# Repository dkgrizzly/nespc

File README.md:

# NES as an 8-Bit PC

This is very much a work in progress, and should be treated as such.

Based on the work done by [Joseph Marlin](https://github.com/jmarlin/) on his YouTube channel [TrackZero](https://www.youtube.com/c/TrackZeroFutzin).
Attaching a standard floppy disk controller (FDC) to a NES-001 game console with BASIC and Monitor in ROM.

I've separated the FDC to a mezzanine card which can be extended outside the case on a 40-pin IDC cable.
Partly due to the relative scarcity of the chips, and partly due to the complexity of the signal routing involved.
The FDC and additonal expansion cards share an 8-bit data and 8-bit address bus. The bus has eight select lines in addition to the FDC selects.

Expansion cards should be connected with 40-pin IDC edge connectors. The expansion bus cable should have three twists as show in expansion.txt.

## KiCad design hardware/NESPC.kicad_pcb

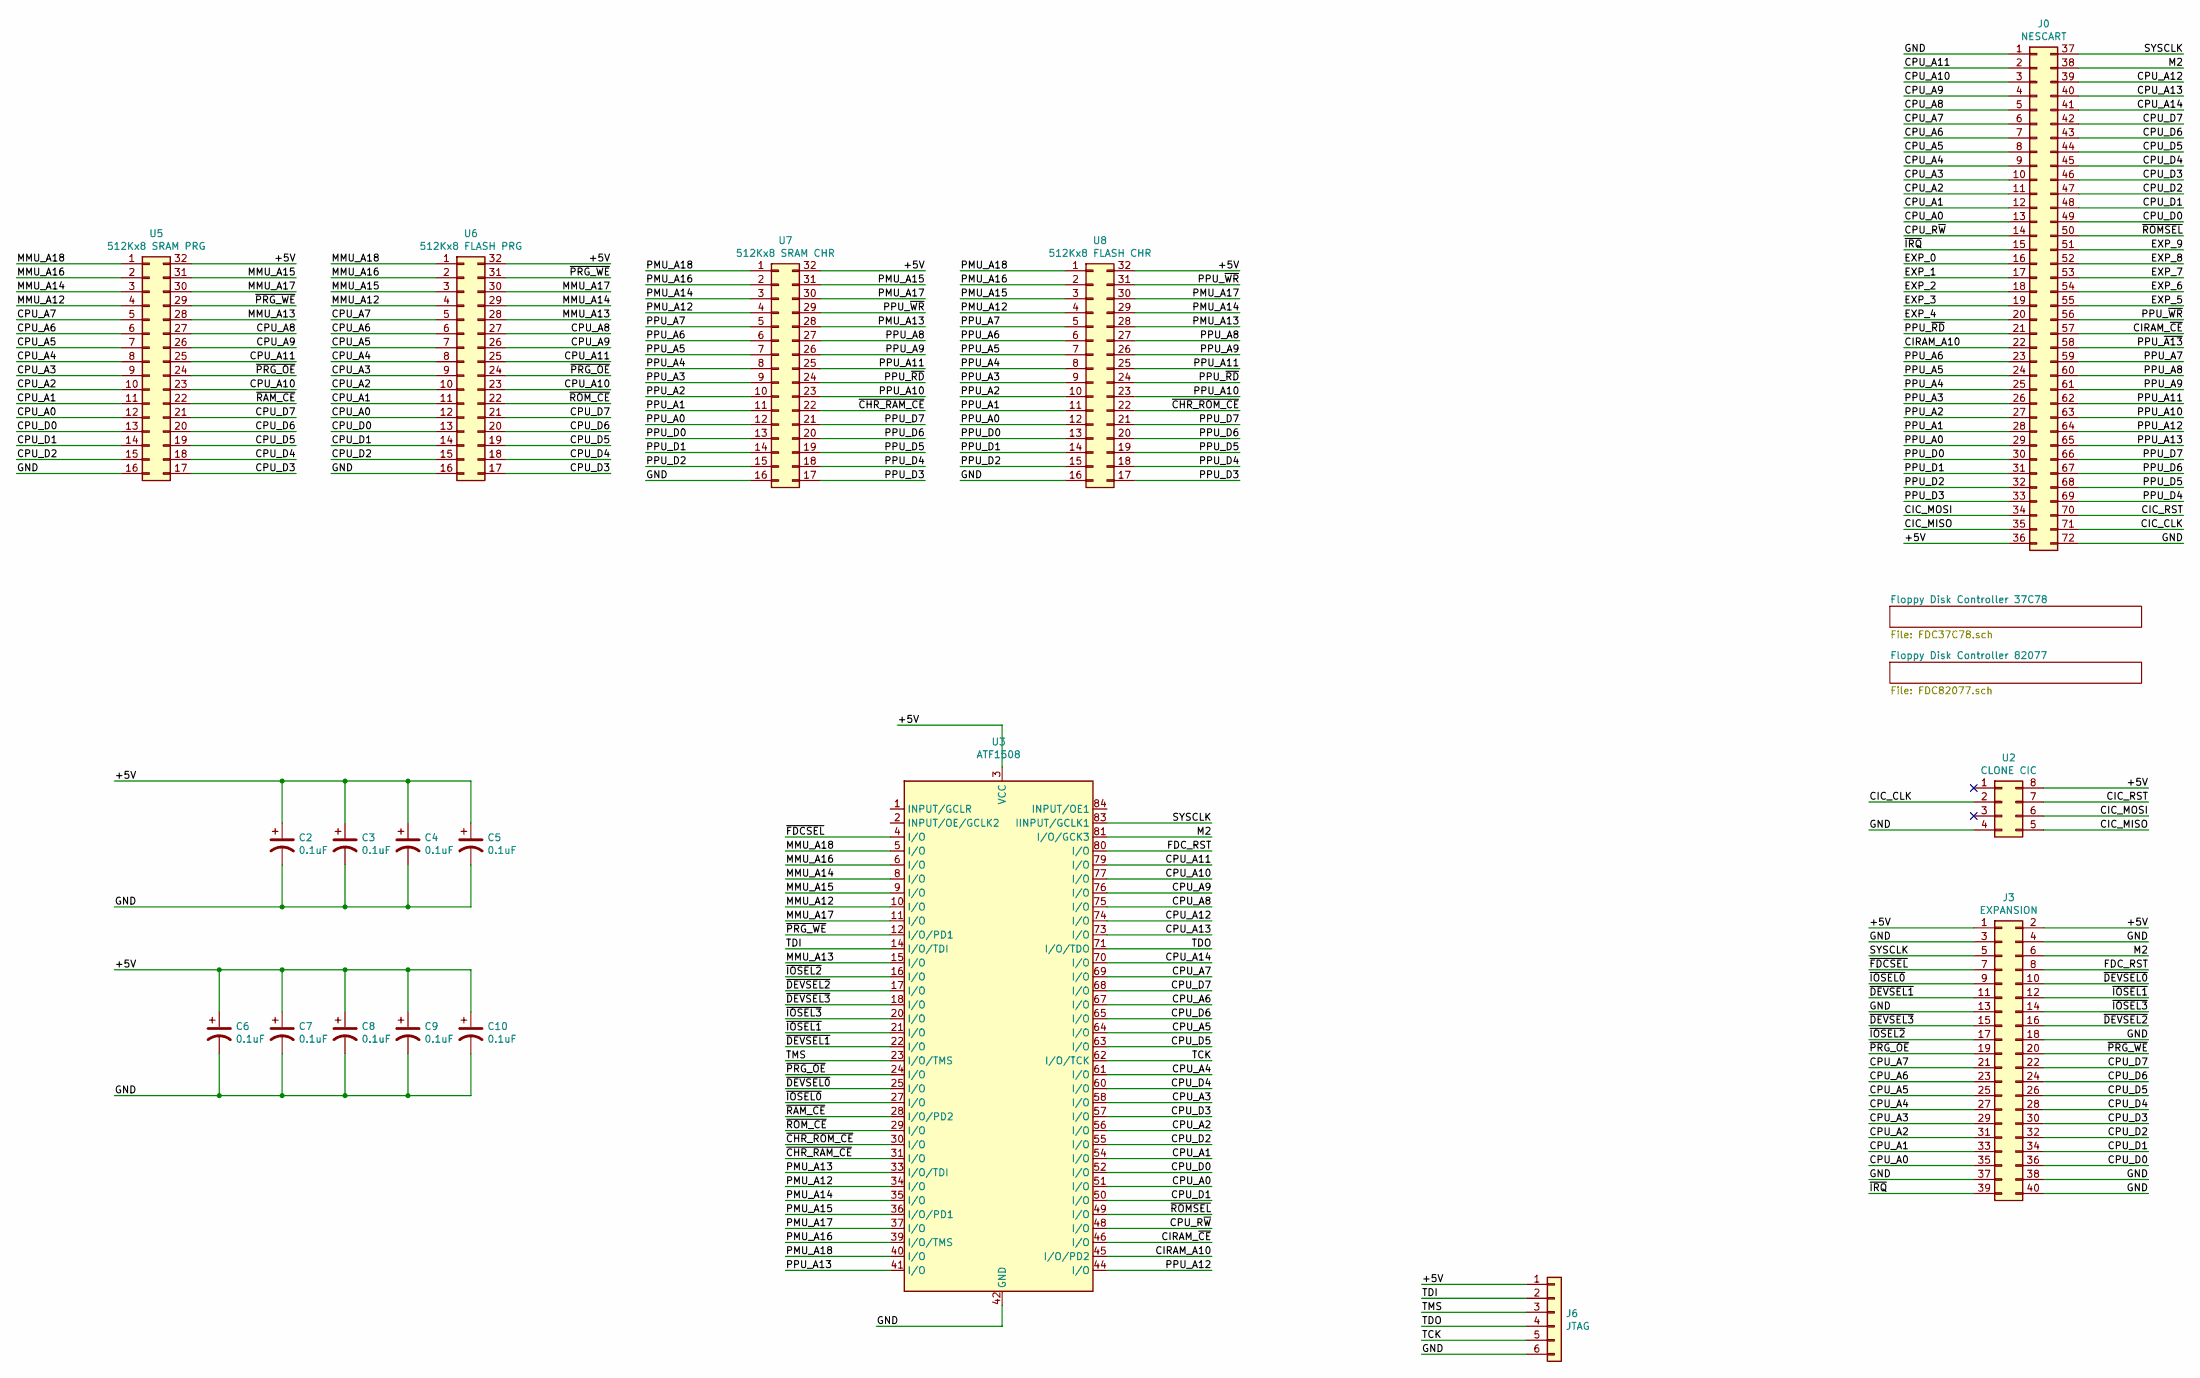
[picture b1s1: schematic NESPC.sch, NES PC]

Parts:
C2, C3, C4, C5, C6, C7, C8, C9, C10: 0.1uF; C_0603_1608Metric_Pad1.08x0.95mm_HandSolder
J0: NESCART; NES_CART
J3: EXPANSION; PinHeader_2x20_P2.54mm_Vertical
J6: JTAG; PinHeader_1x06_P2.54mm_Vertical
U2: CLONE CIC; DIP-8_W7.62mm
U3: ATF1508; PLCC-84
U5: 512Kx8 SRAM PRG; DIP-32_W15.24mm
U6: 512Kx8 FLASH PRG; DIP-32_W15.24mm
U7: 512Kx8 SRAM CHR; DIP-32_W15.24mm
U8: 512Kx8 FLASH CHR; DIP-32_W15.24mm

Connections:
/+5V: C2.1, C3.1, C4.1, C5.1, C6.1, C7.1, C8.1, C9.1, C10.1, J0.36, J3.1, J3.2, J6.1, U2.8, U3.3 (VCC), U3.13 (VCC), U3.26 (VCC), U3.38 (VCC), U3.43 (VCC), U3.53 (VCC), U3.66 (VCC), U3.78 (VCC), U5.32, U6.32, U7.32, U8.32
/CIC_CLK: J0.71, U2.2
/CIC_MISO: J0.35, U2.5
/CIC_MOSI: J0.34, U2.6
/CIC_RST: J0.70, U2.7
/CIRAM_A10: J0.22, U3.45 (I/O/PD2)
/CIRAM_~CE: J0.57, U3.46 (I/O)
/CPU_A0: J0.13, J3.35, U3.51 (I/O), U5.12, U6.12
/CPU_A1: J0.12, J3.33, U3.54 (I/O), U5.11, U6.11
/CPU_A2: J0.11, J3.31, U3.56 (I/O), U5.10, U6.10
/CPU_A3: J0.10, J3.29, U3.58 (I/O), U5.9, U6.9
/CPU_A4: J0.9, J3.27, U3.61 (I/O), U5.8, U6.8
/CPU_A5: J0.8, J3.25, U3.64 (I/O), U5.7, U6.7
/CPU_A6: J0.7, J3.23, U3.67 (I/O), U5.6, U6.6
/CPU_A7: J0.6, J3.21, U3.69 (I/O), U5.5, U6.5
/CPU_A8: J0.5, U3.75 (I/O), U5.27, U6.27
/CPU_A9: J0.4, U3.76 (I/O), U5.26, U6.26
/CPU_A10: J0.3, U3.77 (I/O), U5.23, U6.23
/CPU_A11: J0.2, U3.79 (I/O), U5.25, U6.25
/CPU_A12: J0.39, U3.74 (I/O)
/CPU_A13: J0.40, U3.73 (I/O)
/CPU_A14: J0.41, U3.70 (I/O)
/CPU_D0: J0.49, J3.36, U3.52 (I/O), U5.13, U6.13
/CPU_D1: J0.48, J3.34, U3.50 (I/O), U5.14, U6.14
/CPU_D2: J0.47, J3.32, U3.55 (I/O), U5.15, U6.15
/CPU_D3: J0.46, J3.30, U3.57 (I/O), U5.17, U6.17
/CPU_D4: J0.45, J3.28, U3.60 (I/O), U5.18, U6.18
/CPU_D5: J0.44, J3.26, U3.63 (I/O), U5.19, U6.19
/CPU_D6: J0.43, J3.24, U3.65 (I/O), U5.20, U6.20
/CPU_D7: J0.42, J3.22, U3.68 (I/O), U5.21, U6.21
/CPU_R~W: J0.14, U3.48 (I/O)
/EXP_0: J0.16
/EXP_1: J0.17
/EXP_2: J0.18
/EXP_3: J0.19
/EXP_4: J0.20
/EXP_5: J0.55
/EXP_6: J0.54
/EXP_7: J0.53
/EXP_8: J0.52
/EXP_9: J0.51
/FDC_RST: J3.8, U3.80 (I/O)
/GND: C2.2, C3.2, C4.2, C5.2, C6.2, C7.2, C8.2, C9.2, C10.2, J0.1, J0.72, J3.3, J3.4, J3.13, J3.18, J3.37, J3.38, J3.40, J6.6, U2.4, U3.7 (GND), U3.19 (GND), U3.32 (GND), U3.42 (GND), U3.47 (GND), U3.59 (GND), U3.72 (GND), U3.82 (GND), U5.16, U6.16, U7.16, U8.16
/M2: J0.38, J3.6, U3.81 (I/O/GCK3)
/MMU_A12: U3.10 (I/O), U5.4, U6.4
/MMU_A13: U3.15 (I/O), U5.28, U6.28
/MMU_A14: U3.8 (I/O), U5.3, U6.29
/MMU_A15: U3.9 (I/O), U5.31, U6.3
/MMU_A16: U3.6 (I/O), U5.2, U6.2
/MMU_A17: U3.11 (I/O), U5.30, U6.30
/MMU_A18: U3.5 (I/O), U5.1, U6.1
/PMU_A12: U3.34 (I/O), U7.4, U8.4
/PMU_A13: U3.33 (I/O/TDI), U7.28, U8.28
/PMU_A14: U3.35 (I/O), U7.3, U8.29
/PMU_A15: U3.36 (I/O/PD1), U7.31, U8.3
/PMU_A16: U3.39 (I/O/TMS), U7.2, U8.2
/PMU_A17: U3.37 (I/O), U7.30, U8.30
/PMU_A18: U3.40 (I/O), U7.1, U8.1
/PPU_A0: J0.29, U7.12, U8.12
/PPU_A1: J0.28, U7.11, U8.11
/PPU_A2: J0.27, U7.10, U8.10
/PPU_A3: J0.26, U7.9, U8.9
/PPU_A4: J0.25, U7.8, U8.8
/PPU_A5: J0.24, U7.7, U8.7
/PPU_A6: J0.23, U7.6, U8.6
/PPU_A7: J0.59, U7.5, U8.5
/PPU_A8: J0.60, U7.27, U8.27
/PPU_A9: J0.61, U7.26, U8.26
/PPU_A10: J0.63, U7.23, U8.23
/PPU_A11: J0.62, U7.25, U8.25
/PPU_A12: J0.64, U3.44 (I/O)
/PPU_A13: J0.65, U3.41 (I/O)
/PPU_D0: J0.30, U7.13, U8.13
/PPU_D1: J0.31, U7.14, U8.14
/PPU_D2: J0.32, U7.15, U8.15
/PPU_D3: J0.33, U7.17, U8.17
/PPU_D4: J0.69, U7.18, U8.18
/PPU_D5: J0.68, U7.19, U8.19
/PPU_D6: J0.67, U7.20, U8.20
/PPU_D7: J0.66, U7.21, U8.21
/PPU_~A13: J0.58
/PPU_~RD: J0.21, U7.24, U8.24
/PPU_~WR: J0.56, U7.29, U8.31
/SYSCLK: J0.37, J3.5, U3.83 (IINPUT/GCLK1)
/TCK: J6.5, U3.62 (I/O/TCK)
/TDI: J6.2, U3.14 (I/O/TDI)
/TDO: J6.4, U3.71 (I/O/TDO)
/TMS: J6.3, U3.23 (I/O/TMS)
/~CHR_RAM_CE: U3.31 (I/O), U7.22
/~CHR_ROM_CE: U3.30 (I/O), U8.22
/~DEVSEL0: J3.10, U3.25 (I/O)
/~DEVSEL1: J3.11, U3.22 (I/O)
/~DEVSEL2: J3.16, U3.17 (I/O)
/~DEVSEL3: J3.15, U3.18 (I/O)
/~FDCSEL: J3.7, U3.4 (I/O)
/~IOSEL0: J3.9, U3.27 (I/O)
/~IOSEL1: J3.12, U3.21 (I/O)
/~IOSEL2: J3.17, U3.16 (I/O)
/~IOSEL3: J3.14, U3.20 (I/O)
/~IRQ: J0.15, J3.39
/~PRG_OE: J3.19, U3.24 (I/O), U5.24, U6.24
/~PRG_WE: J3.20, U3.12 (I/O/PD1), U5.29, U6.31
/~RAM_CE: U3.28 (I/O/PD2), U5.22
/~ROMSEL: J0.50, U3.49 (I/O)
/~ROM_CE: U3.29 (I/O), U6.22

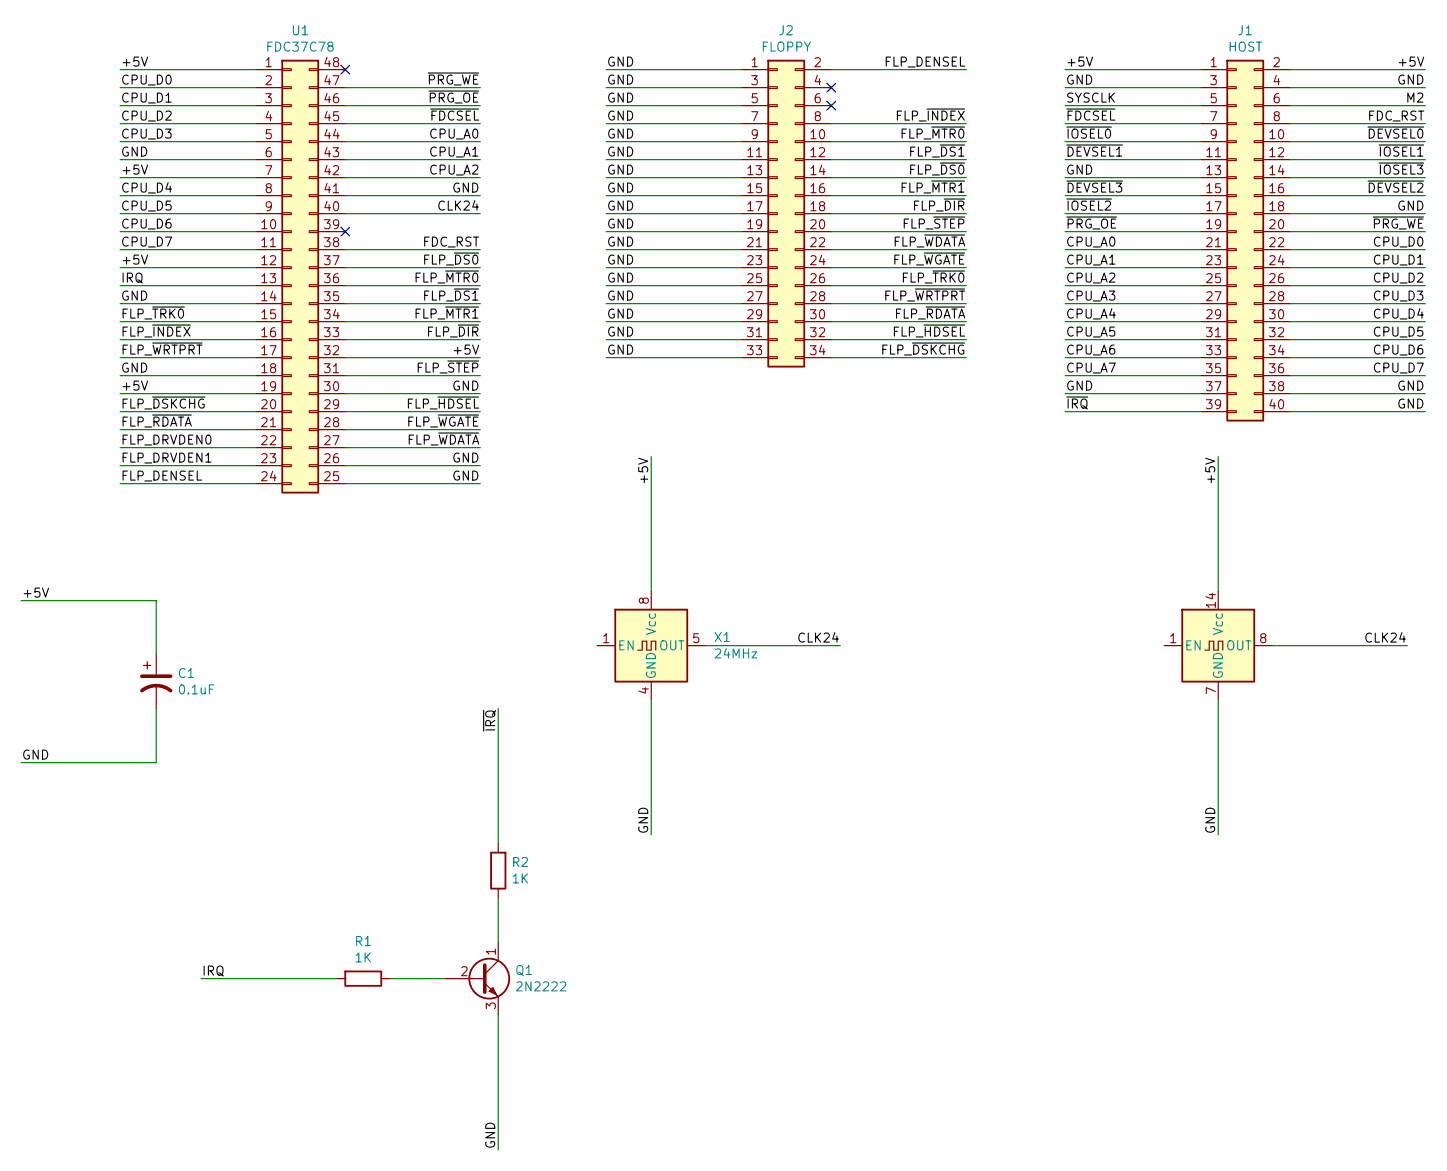
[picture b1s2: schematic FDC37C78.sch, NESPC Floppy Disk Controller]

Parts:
C1: 0.1uF; C_0603_1608Metric_Pad1.08x0.95mm_HandSolder
J1: HOST; PinHeader_2x20_P2.54mm_Vertical
J2: FLOPPY; PinHeader_2x17_P2.54mm_Vertical
Q1: 2N2222; TO-92S_Wide
R1, R2: 1K; R_0603_1608Metric_Pad0.98x0.95mm_HandSolder
U1: FDC37C78; LQFP-48_7x7mm_P0.5mm
X1: 24MHz; Oscillator_DIP-8
X2: CXO_DIP14; Oscillator_DIP-14

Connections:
/Floppy Disk Controller 37C78/+5V: C1.1, J1.1, J1.2, U1.1, U1.7, U1.12, U1.19, U1.32, X1.8 (Vcc), X2.14 (Vcc)
/Floppy Disk Controller 37C78/CLK24: U1.40, X1.5 (OUT), X2.8 (OUT)
/Floppy Disk Controller 37C78/CPU_A0: J1.21, U1.44
/Floppy Disk Controller 37C78/CPU_A1: J1.23, U1.43
/Floppy Disk Controller 37C78/CPU_A2: J1.25, U1.42
/Floppy Disk Controller 37C78/CPU_A3: J1.27
/Floppy Disk Controller 37C78/CPU_A4: J1.29
/Floppy Disk Controller 37C78/CPU_A5: J1.31
/Floppy Disk Controller 37C78/CPU_A6: J1.33
/Floppy Disk Controller 37C78/CPU_A7: J1.35
/Floppy Disk Controller 37C78/CPU_D0: J1.22, U1.2
/Floppy Disk Controller 37C78/CPU_D1: J1.24, U1.3
/Floppy Disk Controller 37C78/CPU_D2: J1.26, U1.4
/Floppy Disk Controller 37C78/CPU_D3: J1.28, U1.5
/Floppy Disk Controller 37C78/CPU_D4: J1.30, U1.8
/Floppy Disk Controller 37C78/CPU_D5: J1.32, U1.9
/Floppy Disk Controller 37C78/CPU_D6: J1.34, U1.10
/Floppy Disk Controller 37C78/CPU_D7: J1.36, U1.11
/Floppy Disk Controller 37C78/FDC_RST: J1.8, U1.38
/Floppy Disk Controller 37C78/FLP_DENSEL: J2.2, U1.24
/Floppy Disk Controller 37C78/FLP_DRVDEN0: U1.22
/Floppy Disk Controller 37C78/FLP_DRVDEN1: U1.23
/Floppy Disk Controller 37C78/FLP_~DIR: J2.18, U1.33
/Floppy Disk Controller 37C78/FLP_~DS0: J2.14, U1.37
/Floppy Disk Controller 37C78/FLP_~DS1: J2.12, U1.35
/Floppy Disk Controller 37C78/FLP_~DSKCHG: J2.34, U1.20
/Floppy Disk Controller 37C78/FLP_~HDSEL: J2.32, U1.29
/Floppy Disk Controller 37C78/FLP_~INDEX: J2.8, U1.16
/Floppy Disk Controller 37C78/FLP_~MTR0: J2.10, U1.36
/Floppy Disk Controller 37C78/FLP_~MTR1: J2.16, U1.34
/Floppy Disk Controller 37C78/FLP_~RDATA: J2.30, U1.21
/Floppy Disk Controller 37C78/FLP_~STEP: J2.20, U1.31
/Floppy Disk Controller 37C78/FLP_~TRK0: J2.26, U1.15
/Floppy Disk Controller 37C78/FLP_~WDATA: J2.22, U1.27
/Floppy Disk Controller 37C78/FLP_~WGATE: J2.24, U1.28
/Floppy Disk Controller 37C78/FLP_~WRTPRT: J2.28, U1.17
/Floppy Disk Controller 37C78/GND: C1.2, J1.3, J1.4, J1.13, J1.18, J1.37, J1.38, J1.40, J2.1, J2.3, J2.5, J2.7, J2.9, J2.11, J2.13, J2.15, J2.17, J2.19, J2.21, J2.23, J2.25, J2.27, J2.29, J2.31, J2.33, Q1.3 (E), U1.6, U1.14, U1.18, U1.25, U1.26, U1.30, U1.41, X1.4 (GND), X2.7 (GND)
/Floppy Disk Controller 37C78/IRQ: R1.2, U1.13
/Floppy Disk Controller 37C78/M2: J1.6
/Floppy Disk Controller 37C78/SYSCLK: J1.5
/Floppy Disk Controller 37C78/~DEVSEL0: J1.10
/Floppy Disk Controller 37C78/~DEVSEL1: J1.11
/Floppy Disk Controller 37C78/~DEVSEL2: J1.16
/Floppy Disk Controller 37C78/~DEVSEL3: J1.15
/Floppy Disk Controller 37C78/~FDCSEL: J1.7, U1.45
/Floppy Disk Controller 37C78/~IOSEL0: J1.9
/Floppy Disk Controller 37C78/~IOSEL1: J1.12
/Floppy Disk Controller 37C78/~IOSEL2: J1.17
/Floppy Disk Controller 37C78/~IOSEL3: J1.14
/Floppy Disk Controller 37C78/~IRQ: J1.39, R2.2
/Floppy Disk Controller 37C78/~PRG_OE: J1.19, U1.46
/Floppy Disk Controller 37C78/~PRG_WE: J1.20, U1.47
unnamed: Q1.1 (C), R2.1
unnamed: Q1.2 (B), R1.1

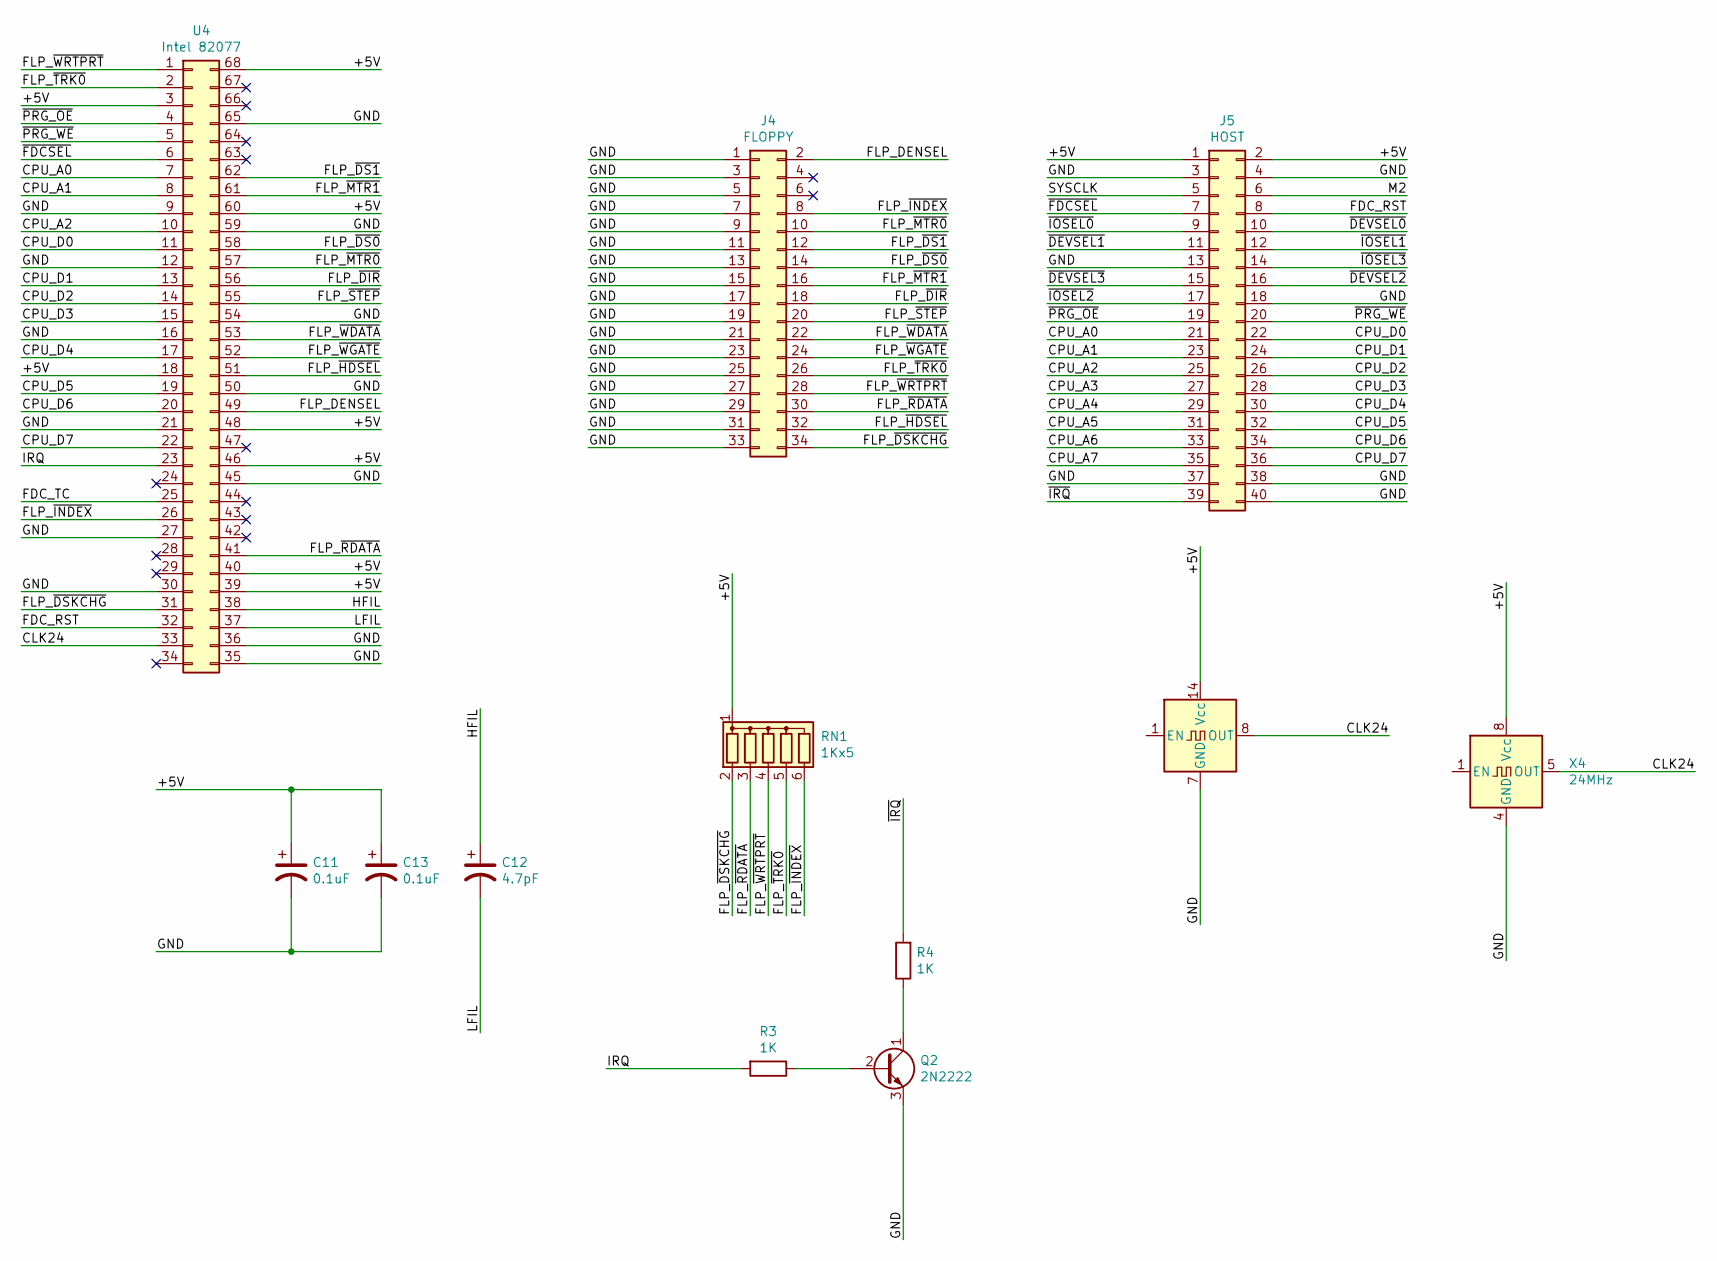
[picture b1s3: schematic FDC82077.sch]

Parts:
C11, C13: 0.1uF; C_0603_1608Metric_Pad1.08x0.95mm_HandSolder
C12: 4.7pF; C_0603_1608Metric_Pad1.08x0.95mm_HandSolder
J4: FLOPPY; PinHeader_2x17_P2.54mm_Vertical
J5: HOST; PinHeader_2x20_P2.54mm_Vertical
Q2: 2N2222; TO-92S_Wide
R3, R4: 1K; R_0603_1608Metric_Pad0.98x0.95mm_HandSolder
RN1: 1Kx5; R_Array_SIP6
U4: Intel 82077; PLCC-68
X3: CXO_DIP14; Oscillator_DIP-14
X4: 24MHz; Oscillator_DIP-8

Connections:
/Floppy Disk Controller 82077/+5V: C11.1, C13.1, J5.1, J5.2, RN1.1 (common), U4.3, U4.18, U4.39, U4.40, U4.46, U4.48, U4.60, U4.68, X3.14 (Vcc), X4.8 (Vcc)
/Floppy Disk Controller 82077/CLK24: U4.33, X3.8 (OUT), X4.5 (OUT)
/Floppy Disk Controller 82077/CPU_A0: J5.21, U4.7
/Floppy Disk Controller 82077/CPU_A1: J5.23, U4.8
/Floppy Disk Controller 82077/CPU_A2: J5.25, U4.10
/Floppy Disk Controller 82077/CPU_A3: J5.27
/Floppy Disk Controller 82077/CPU_A4: J5.29
/Floppy Disk Controller 82077/CPU_A5: J5.31
/Floppy Disk Controller 82077/CPU_A6: J5.33
/Floppy Disk Controller 82077/CPU_A7: J5.35
/Floppy Disk Controller 82077/CPU_D0: J5.22, U4.11
/Floppy Disk Controller 82077/CPU_D1: J5.24, U4.13
/Floppy Disk Controller 82077/CPU_D2: J5.26, U4.14
/Floppy Disk Controller 82077/CPU_D3: J5.28, U4.15
/Floppy Disk Controller 82077/CPU_D4: J5.30, U4.17
/Floppy Disk Controller 82077/CPU_D5: J5.32, U4.19
/Floppy Disk Controller 82077/CPU_D6: J5.34, U4.20
/Floppy Disk Controller 82077/CPU_D7: J5.36, U4.22
/Floppy Disk Controller 82077/FDC_RST: J5.8, U4.32
/Floppy Disk Controller 82077/FDC_TC: U4.25
/Floppy Disk Controller 82077/FLP_DENSEL: J4.2, U4.49
/Floppy Disk Controller 82077/FLP_~DIR: J4.18, U4.56
/Floppy Disk Controller 82077/FLP_~DS0: J4.14, U4.58
/Floppy Disk Controller 82077/FLP_~DS1: J4.12, U4.62
/Floppy Disk Controller 82077/FLP_~DSKCHG: J4.34, RN1.2 (R1), U4.31
/Floppy Disk Controller 82077/FLP_~HDSEL: J4.32, U4.51
/Floppy Disk Controller 82077/FLP_~INDEX: J4.8, RN1.6 (R5), U4.26
/Floppy Disk Controller 82077/FLP_~MTR0: J4.10, U4.57
/Floppy Disk Controller 82077/FLP_~MTR1: J4.16, U4.61
/Floppy Disk Controller 82077/FLP_~RDATA: J4.30, RN1.3 (R2), U4.41
/Floppy Disk Controller 82077/FLP_~STEP: J4.20, U4.55
/Floppy Disk Controller 82077/FLP_~TRK0: J4.26, RN1.5 (R4), U4.2
/Floppy Disk Controller 82077/FLP_~WDATA: J4.22, U4.53
/Floppy Disk Controller 82077/FLP_~WGATE: J4.24, U4.52
/Floppy Disk Controller 82077/FLP_~WRTPRT: J4.28, RN1.4 (R3), U4.1
/Floppy Disk Controller 82077/GND: C11.2, C13.2, J4.1, J4.3, J4.5, J4.7, J4.9, J4.11, J4.13, J4.15, J4.17, J4.19, J4.21, J4.23, J4.25, J4.27, J4.29, J4.31, J4.33, J5.3, J5.4, J5.13, J5.18, J5.37, J5.38, J5.40, Q2.3 (E), U4.9, U4.12, U4.16, U4.21, U4.27, U4.30, U4.35, U4.36, U4.45, U4.50, U4.54, U4.59, U4.65, X3.7 (GND), X4.4 (GND)
/Floppy Disk Controller 82077/HFIL: C12.1, U4.38
/Floppy Disk Controller 82077/IRQ: R3.2, U4.23
/Floppy Disk Controller 82077/LFIL: C12.2, U4.37
/Floppy Disk Controller 82077/M2: J5.6
/Floppy Disk Controller 82077/SYSCLK: J5.5
/Floppy Disk Controller 82077/~DEVSEL0: J5.10
/Floppy Disk Controller 82077/~DEVSEL1: J5.11
/Floppy Disk Controller 82077/~DEVSEL2: J5.16
/Floppy Disk Controller 82077/~DEVSEL3: J5.15
/Floppy Disk Controller 82077/~FDCSEL: J5.7, U4.6
/Floppy Disk Controller 82077/~IOSEL0: J5.9
/Floppy Disk Controller 82077/~IOSEL1: J5.12
/Floppy Disk Controller 82077/~IOSEL2: J5.17
/Floppy Disk Controller 82077/~IOSEL3: J5.14
/Floppy Disk Controller 82077/~IRQ: J5.39, R4.2
/Floppy Disk Controller 82077/~PRG_OE: J5.19, U4.4
/Floppy Disk Controller 82077/~PRG_WE: J5.20, U4.5
unnamed: Q2.1 (C), R4.1
unnamed: Q2.2 (B), R3.1

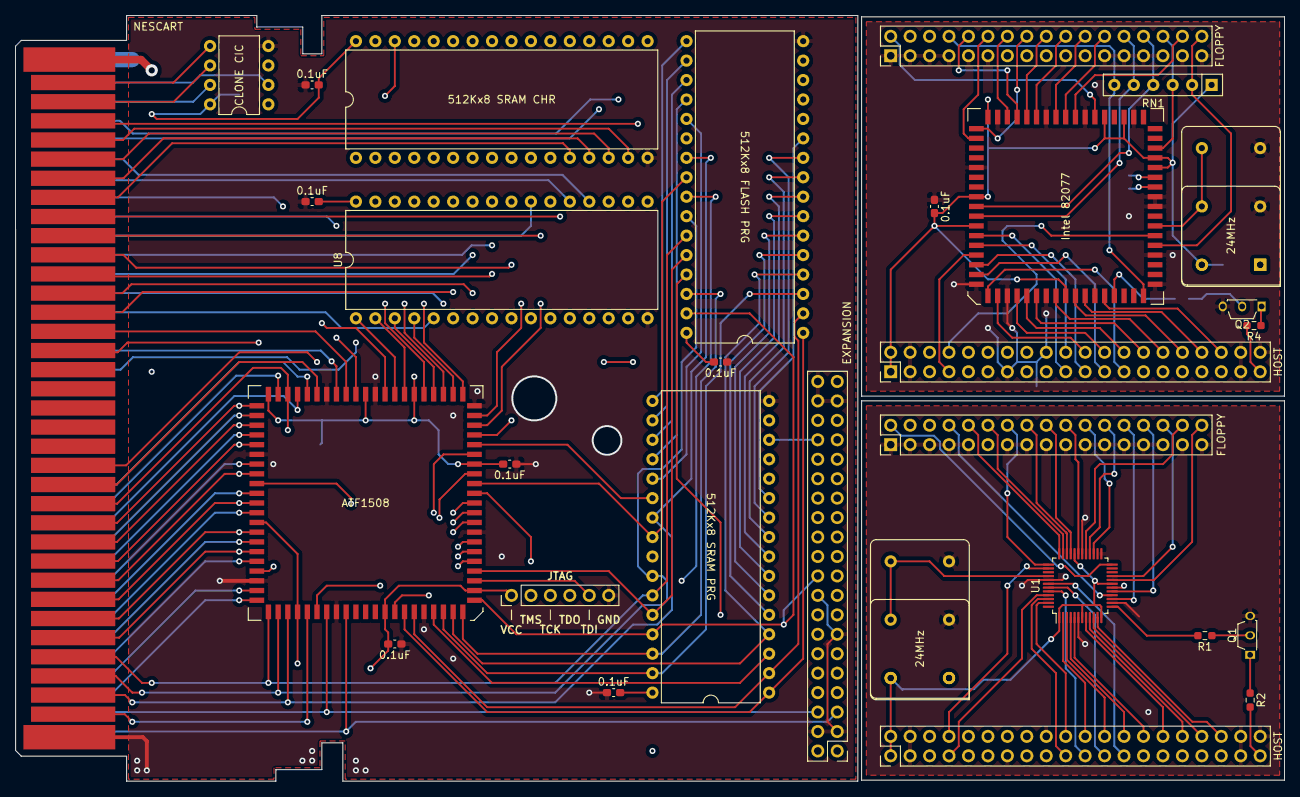
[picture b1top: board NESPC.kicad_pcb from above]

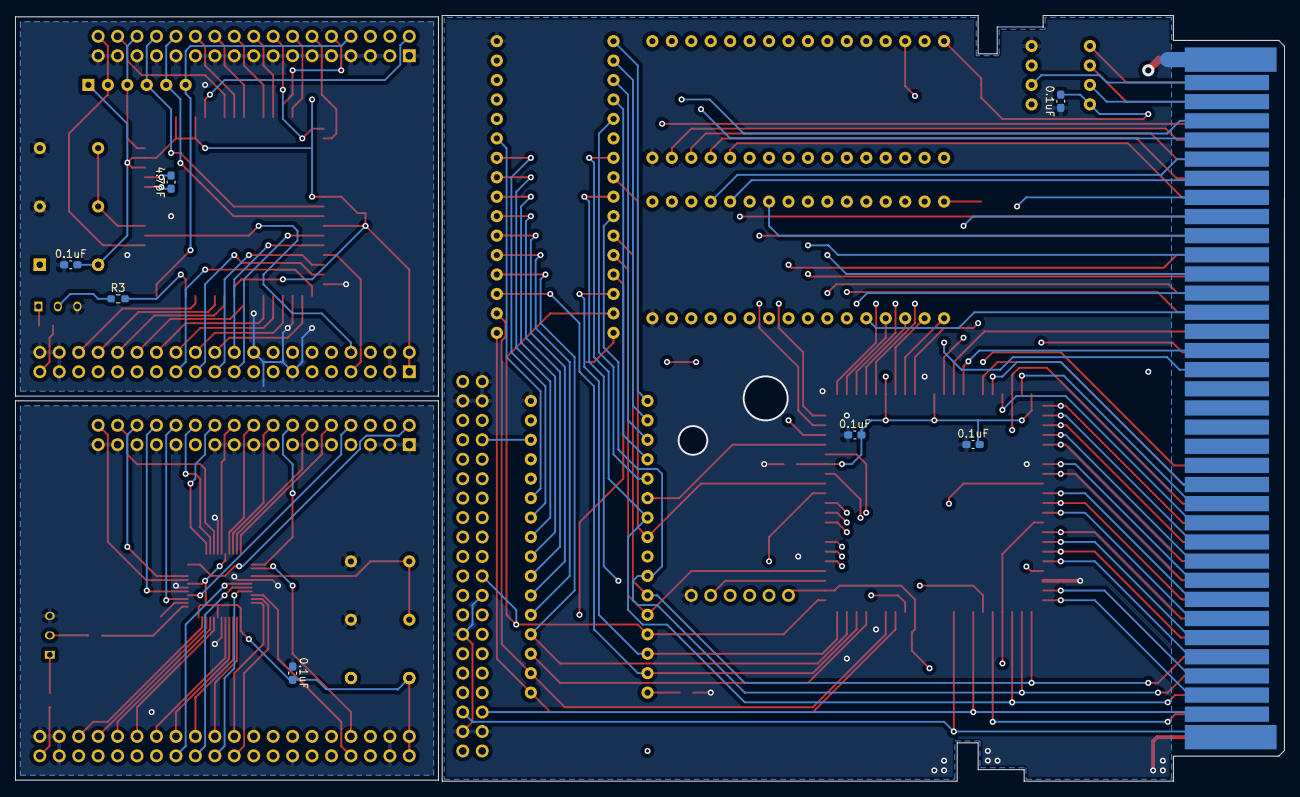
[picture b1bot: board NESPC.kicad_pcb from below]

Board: 4 copper layers, 165.7 x 100.0 mm, 39 parts (7 on the bottom side), 170 nets.

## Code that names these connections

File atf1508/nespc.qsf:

# -------------------------------------------------------------------------- #
#
# Copyright (C) 1991-2013 Altera Corporation
# Your use of Altera Corporation's design tools, logic functions 
# and other software and tools, and its AMPP partner logic 
# functions, and any output files from any of the foregoing 
# (including device programming or simulation files), and any 
# associated documentation or information are expressly subject 
# to the terms and conditions of the Altera Program License 
# Subscription Agreement, Altera MegaCore Function License 
# Agreement, or other applicable license agreement, including, 
# without limitation, that your use is for the sole purpose of 
# programming logic devices manufactured by Altera and sold by 
# Altera or its authorized distributors.  Please refer to the 
# applicable agreement for further details.
#
# -------------------------------------------------------------------------- #
#
# Quartus II 64-Bit
# Version 13.0.1 Build 232 06/12/2013 Service Pack 1 SJ Web Edition
# Date created = 01:31:10  October 17, 2022
#
# -------------------------------------------------------------------------- #
#
# Notes:
#
# 1) The default values for assignments are stored in the file:
#		nespc_assignment_defaults.qdf
#    If this file doesn't exist, see file:
#		assignment_defaults.qdf
#
# 2) Altera recommends that you do not modify this file. This
#    file is updated automatically by the Quartus II software
#    and any changes you make may be lost or overwritten.
#
# -------------------------------------------------------------------------- #


set_global_assignment -name FAMILY MAX7000S
set_global_assignment -name DEVICE "EPM7128SLC84-7"
set_global_assignment -name TOP_LEVEL_ENTITY nespc
set_global_assignment -name ORIGINAL_QUARTUS_VERSION "13.0 SP1"
set_global_assignment -name PROJECT_CREATION_TIME_DATE "01:31:10  OCTOBER 17, 2022"
set_global_assignment -name LAST_QUARTUS_VERSION "13.0 SP1"
set_global_assignment -name PROJECT_OUTPUT_DIRECTORY output_files
set_global_assignment -name ERROR_CHECK_FREQUENCY_DIVISOR "-1"
set_global_assignment -name MIN_CORE_JUNCTION_TEMP 0
set_global_assignment -name MAX_CORE_JUNCTION_TEMP 85
set_global_assignment -name MAX7000_DEVICE_IO_STANDARD TTL
set_location_assignment PIN_4 -to FDC_nCE
set_location_assignment PIN_5 -to MMU_A[6]
set_location_assignment PIN_6 -to MMU_A[4]
set_location_assignment PIN_8 -to MMU_A[2]
set_location_assignment PIN_9 -to MMU_A[3]
set_location_assignment PIN_10 -to MMU_A[0]
set_location_assignment PIN_11 -to MMU_A[5]
set_location_assignment PIN_12 -to CPU_nWR
set_location_assignment PIN_15 -to MMU_A[1]
set_location_assignment PIN_16 -to SEL[4]
set_location_assignment PIN_17 -to SEL[5]
set_location_assignment PIN_18 -to SEL[7]
set_location_assignment PIN_20 -to SEL[6]
set_location_assignment PIN_21 -to SEL[2]
set_location_assignment PIN_22 -to SEL[3]
set_location_assignment PIN_24 -to CPU_nRD
set_location_assignment PIN_25 -to SEL[1]
set_location_assignment PIN_27 -to SEL[0]
set_location_assignment PIN_28 -to PRG_RAM_nCE
set_location_assignment PIN_29 -to PRG_ROM_nCE
set_location_assignment PIN_30 -to CHR_ROM_nCE
set_location_assignment PIN_31 -to CHR_RAM_nCE
set_location_assignment PIN_33 -to PPU_A13
set_location_assignment PIN_34 -to PMU_A[0]
set_location_assignment PIN_35 -to PMU_A[2]
set_location_assignment PIN_36 -to PMU_A[3]
set_location_assignment PIN_37 -to PMU_A[5]
set_location_assignment PIN_39 -to PMU_A[4]
set_location_assignment PIN_40 -to PMU_A[6]
set_location_assignment PIN_41 -to PMU_A[1]
set_location_assignment PIN_44 -to PPU_A12
set_location_assignment PIN_45 -to CI_RAM_A10
set_location_assignment PIN_46 -to CI_RAM_nCE
set_location_assignment PIN_48 -to CPU_RW
set_location_assignment PIN_49 -to nROMSEL
set_location_assignment PIN_50 -to CPU_D[1]
set_location_assignment PIN_51 -to CPU_A[0]
set_location_assignment PIN_52 -to CPU_D[0]
set_location_assignment PIN_54 -to CPU_A[1]
set_location_assignment PIN_55 -to CPU_D[2]
set_location_assignment PIN_56 -to CPU_A[2]
set_location_assignment PIN_57 -to CPU_D[3]
set_location_assignment PIN_58 -to CPU_A[3]
set_location_assignment PIN_60 -to CPU_D[4]
set_location_assignment PIN_61 -to CPU_A[4]
set_location_assignment PIN_63 -to CPU_D[5]
set_location_assignment PIN_64 -to CPU_A[5]
set_location_assignment PIN_65 -to CPU_D[6]
set_location_assignment PIN_67 -to CPU_A[6]
set_location_assignment PIN_68 -to CPU_D[7]
set_location_assignment PIN_69 -to CPU_A[7]
set_location_assignment PIN_70 -to CPU_A[14]
set_location_assignment PIN_73 -to CPU_A[13]
set_location_assignment PIN_74 -to CPU_A[12]
set_location_assignment PIN_75 -to CPU_A[8]
set_location_assignment PIN_76 -to CPU_A[9]
set_location_assignment PIN_77 -to CPU_A[10]
set_location_assignment PIN_79 -to CPU_A[11]
set_location_assignment PIN_80 -to FDC_RST
set_location_assignment PIN_81 -to M2
set_location_assignment PIN_83 -to SYSCLK
set_global_assignment -name SOURCE_FILE nespc.qsf
set_global_assignment -name VERILOG_FILE nespc.v
set_global_assignment -name SDC_FILE nespc.sdc

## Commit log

2022-10-14 CUPL Compliance
2022-10-18 PCB for ATF1508 Based Cart
2022-10-18 FDC wiring
2022-10-18 Cleanup
2022-10-18 Schematic PDF
2022-10-19 Intel 82077 FDC and more rework
2022-10-19 Pin remapping final final final really this time
2022-10-20 Support for remapping $0000-$3FFF if U3 has been replaced
    Replace U3 with a 22V10 to move PPU registers so $0000-$3FFF are available.
2022-10-20 Finalized boards sent out for Rev.0
2022-10-26 Add U3 replacement MOD
